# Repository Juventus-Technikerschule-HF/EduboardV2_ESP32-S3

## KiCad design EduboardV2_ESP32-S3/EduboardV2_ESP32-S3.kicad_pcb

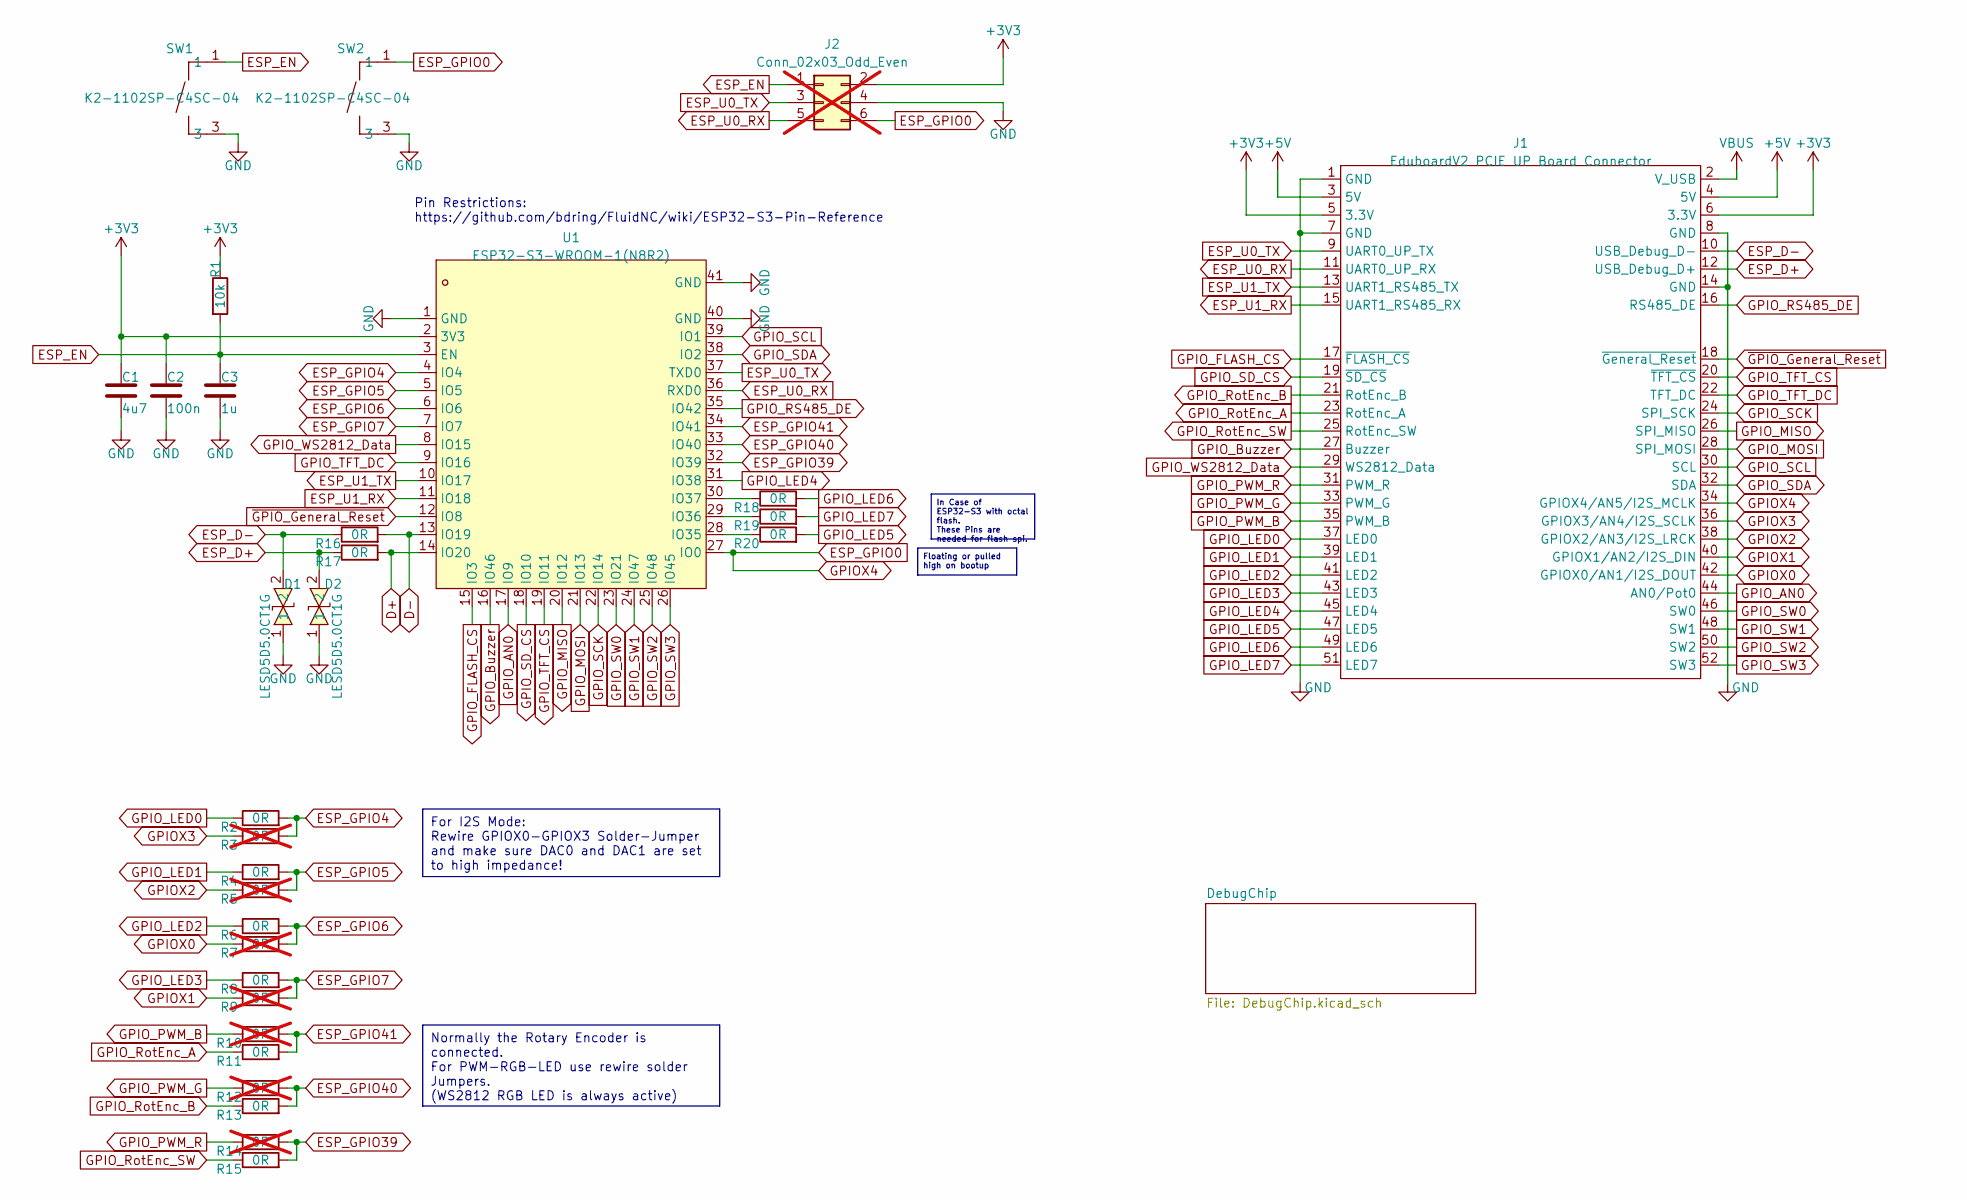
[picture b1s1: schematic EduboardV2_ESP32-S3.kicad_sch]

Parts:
C1: 4u7; C_0805_2012Metric; JLCPCB Part # C76642
C2: 100n; C_0603_1608Metric; JLCPCB Part # C105907
C3: 1u; C_0805_2012Metric; JLCPCB Part # C77083
D1, D2: LESD5D5.0CT1G; SOD-523_L1.2-W0.8-LS1.6-BI; LCSC Part C383211
J1: EduboardV2 PCIE UP Board Connector; mini-PCIe_F1_Full
J2: Conn_02x03_Odd_Even; PinHeader_2x03_P2.54mm_Vertical; not fitted
R1: 10k; R_0402_1005Metric; JLCPCB Part # C71617
R2, R4, R6, R8, R11, R13, R15, R16, R17, R18, R19, R20: 0R; R_0603_1608Metric; LCSC Part C465460
R3, R5, R7, R9, R10, R12, R14: 0R; R_0603_1608Metric; LCSC Part C465460; not fitted
SW1, SW2: K2-1102SP-C4SC-04; KEY-SMD_4P-L6.0-W6.0-P4.50-LS9.5-BL; LCSC Part C127509
U1: ESP32-S3-WROOM-1(N8R2); WIRELM-SMD_ESP32-S3-WROOM-1; LCSC Part C2913204

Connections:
+3V3: C1.2, C2.1, J1.5 (3.3V), J1.6 (3.3V), J2.2, R1.1, U1.2 (3V3)
+5V: J1.3 (5V), J1.4 (5V)
D+: R17.2, U1.14 (IO20)
D-: R16.2, U1.13 (IO19)
ESP_D+: D2.2, J1.12 (USB_Debug_D+), R17.1
ESP_D-: D1.2, J1.10 (USB_Debug_D-), R16.1
ESP_EN: C3.2, J2.1, R1.2, SW1.1, SW1.2, U1.3 (EN)
ESP_GPIO0: J1.34 (GPIOX4/AN5/I2S_MCLK), J2.6, SW2.1, SW2.2, U1.27 (IO0)
ESP_GPIO4: R2.2, R3.2, U1.4 (IO4)
ESP_GPIO5: R4.2, R5.2, U1.5 (IO5)
ESP_GPIO6: R6.2, R7.2, U1.6 (IO6)
ESP_GPIO7: R8.2, R9.2, U1.7 (IO7)
ESP_GPIO39: R14.2, R15.2, U1.32 (IO39)
ESP_GPIO40: R12.2, R13.2, U1.33 (IO40)
ESP_GPIO41: R10.2, R11.2, U1.34 (IO41)
ESP_U0_RX: J1.11 (UART0_UP_RX), J2.5, U1.36 (RXD0)
ESP_U0_TX: J1.9 (UART0_UP_TX), J2.3, U1.37 (TXD0)
ESP_U1_RX: J1.15 (UART1_RS485_RX), U1.11 (IO18)
ESP_U1_TX: J1.13 (UART1_RS485_TX), U1.10 (IO17)
GND: C1.1, C2.2, C3.1, D1.1, D2.1, J1.1 (GND), J1.7 (GND), J1.8 (GND), J1.14 (GND), J2.4, SW1.3, SW1.4, SW2.3, SW2.4, U1.1 (GND), U1.40 (GND), U1.41 (GND)
GPIOX0: J1.42 (GPIOX0/AN1/I2S_DOUT), R7.1
GPIOX1: J1.40 (GPIOX1/AN2/I2S_DIN), R9.1
GPIOX2: J1.38 (GPIOX2/AN3/I2S_LRCK), R5.1
GPIOX3: J1.36 (GPIOX3/AN4/I2S_SCLK), R3.1
GPIO_AN0: J1.44 (AN0/Pot0), U1.17 (IO9)
GPIO_Buzzer: J1.27 (Buzzer), U1.16 (IO46)
GPIO_FLASH_CS: J1.17 (~FLASH_CS), U1.15 (IO3)
GPIO_LED0: J1.37 (LED0), R2.1
GPIO_LED1: J1.39 (LED1), R4.1
GPIO_LED2: J1.41 (LED2), R6.1
GPIO_LED3: J1.43 (LED3), R8.1
GPIO_LED4: J1.45 (LED4), U1.31 (IO38)
GPIO_LED5: J1.47 (LED5), R20.2
GPIO_LED6: J1.49 (LED6), R18.2
GPIO_LED7: J1.51 (LED7), R19.2
GPIO_MISO: J1.26 (SPI_MISO), U1.20 (IO12)
GPIO_MOSI: J1.28 (SPI_MOSI), U1.21 (IO13)
GPIO_PWM_B: J1.35 (PWM_B), R10.1
GPIO_PWM_G: J1.33 (PWM_G), R12.1
GPIO_PWM_R: J1.31 (PWM_R), R14.1
GPIO_RS485_DE: J1.16 (RS485_DE), U1.35 (IO42)
GPIO_RotEnc_A: J1.23 (RotEnc_A), R11.1
GPIO_RotEnc_B: J1.21 (RotEnc_B), R13.1
GPIO_RotEnc_SW: J1.25 (RotEnc_SW), R15.1
GPIO_SCK: J1.24 (SPI_SCK), U1.22 (IO14)
GPIO_SCL: J1.30 (SCL), U1.39 (IO1)
GPIO_SDA: J1.32 (SDA), U1.38 (IO2)
GPIO_SD_CS: J1.19 (~SD_CS), U1.18 (IO10)
GPIO_SW0: J1.46 (SW0), U1.23 (IO21)
GPIO_SW1: J1.48 (SW1), U1.24 (IO47)
GPIO_SW2: J1.50 (SW2), U1.25 (IO48)
GPIO_SW3: J1.52 (SW3), U1.26 (IO45)
GPIO_TFT_CS: J1.20 (~TFT_CS), U1.19 (IO11)
GPIO_TFT_DC: J1.22 (TFT_DC), U1.9 (IO16)
GPIO_WS2812_Data: J1.29 (WS2812_Data), U1.8 (IO15)
unnamed: R20.1, U1.28 (IO35)
unnamed: R19.1, U1.29 (IO36)
unnamed: R18.1, U1.30 (IO37)
VBUS: J1.2 (V_USB)
~GPIO_General_Reset: J1.18 (~General_Reset), U1.12 (IO8)

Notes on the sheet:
For I2S Mode: Rewire GPIOX0-GPIOX3 Solder-Jumper and make sure DAC0 and DAC1 are set to high impedance!
Normally the Rotary Encoder is connected. For PWM-RGB-LED use rewire solder Jumpers. (WS2812 RGB LED is always active)
Floating or pulled high on bootup
In Case of ESP32-S3 with octal flash. These Pins are needed for flash spi.
Pin Restrictions: https://github.com/bdring/FluidNC/wiki/ESP32-S3-Pin-Reference

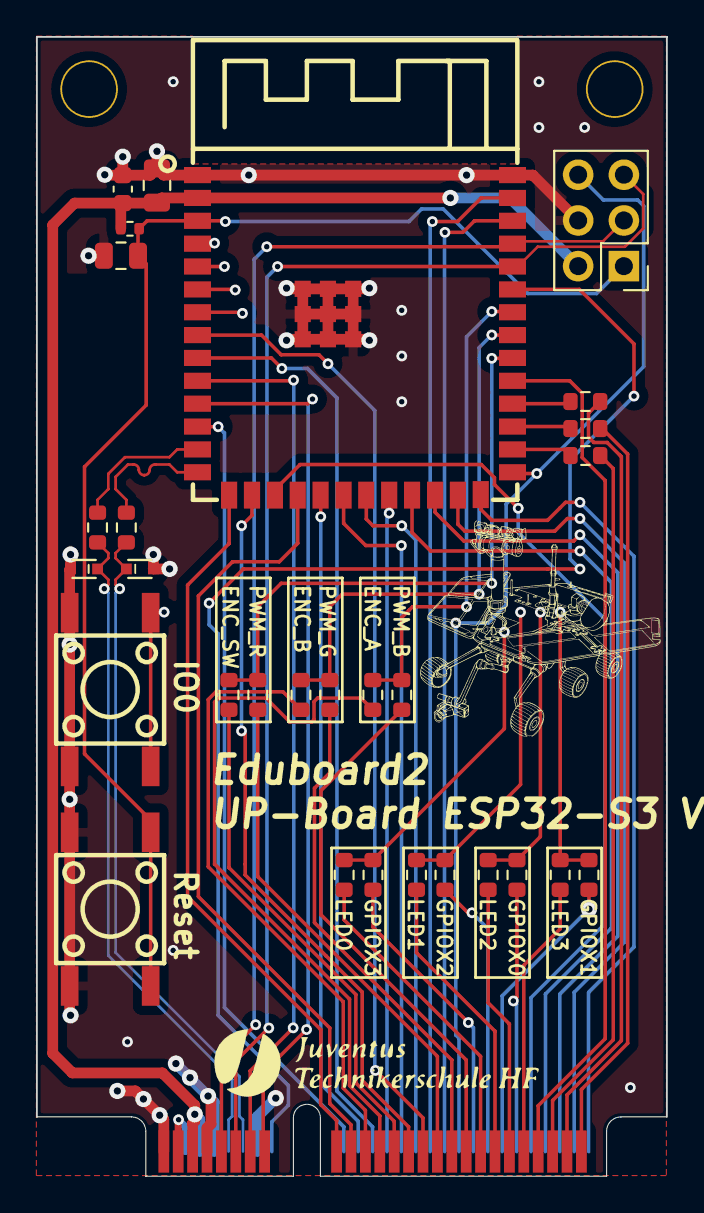
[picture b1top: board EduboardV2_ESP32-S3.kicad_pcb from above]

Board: 4 copper layers, 35.0 x 63.3 mm, 30 parts (0 on the bottom side), 59 nets.

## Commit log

2023-04-27 initial commit of ESP32-S3 UP Board. USB-Serial done. Start distributing pins
2023-04-28 distribute signals to pins
2023-04-28 remove stuff because of gitignore
2023-04-28 add gitignore
2023-05-01 finish schematic. Do Layout
2023-05-02 add logo
2023-05-06 add jumper description on board
2023-06-25 Do all modifications for V1.1 and create production data
2023-06-26 Finalize and order V1.1
2024-07-12 migrate to kicad v8.
